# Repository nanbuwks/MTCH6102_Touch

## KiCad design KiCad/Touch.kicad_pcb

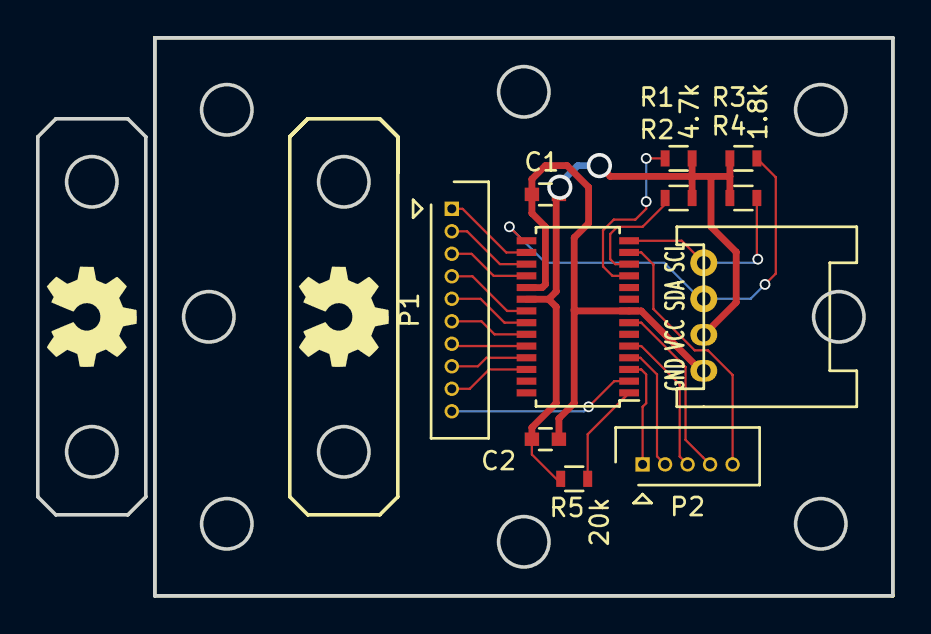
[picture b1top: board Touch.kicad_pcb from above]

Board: 2 copper layers, 47.5 x 31.0 mm, 13 parts (0 on the bottom side), 22 nets.

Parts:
C1: 0.1; C_0603
C2: 10; C_0603
OSHW: 1.1; OSHW_LOGL_SYLK_5mm
OSHW#2: 1.1; OSHW_LOGL_SYLK_5mm
P1: CONN_01X10; Connector_Molex_PicoBlade_53047-1010
P2: CONN_01X05; Connector_Molex_PicoBlade_53047-0510
P3: CONN_01X04; Grove_I2C_Horisontal_4pin_2mmpitch
R1, R2: 4.7k; R_0603
R3, R4: 1.8k; R_0603
R5: 20k; R_0603
U1: MTCH6102_SSOP28; TSSOP-28_4.4x9.7mm_Pitch0.65mm

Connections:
unnamed: C1.1, C2.1, P3.2, R1.1, R2.1, R3.1, R4.1, R5.1, U1.20
unnamed: C1.2, C2.2, P3.1, U1.8, U1.19
unnamed: P1.1, U1.16
unnamed: P1.2, U1.17
unnamed: P1.3, U1.18
unnamed: P1.4, U1.21
unnamed: P1.5, U1.22
unnamed: P1.6, U1.23
unnamed: P1.7, U1.24
unnamed: P1.8, U1.25
unnamed: P1.9, U1.26
unnamed: P1.10, U1.2
unnamed: P2.1, U1.3
unnamed: P2.2, U1.4
unnamed: P2.3, U1.5
unnamed: P2.4, U1.7
unnamed: P2.5, U1.13
unnamed: P3.3, R3.2, U1.15
unnamed: P3.4, R4.2, U1.14
unnamed: R1.2, U1.11
unnamed: R2.2, U1.12
unnamed: R5.2, U1.1

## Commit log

2018-08-20 add FPC connector.
